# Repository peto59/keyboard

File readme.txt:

to update submodule use:
git submodule update --recursive --remote 

TODO:
Add/Move FN to left
Put key names on silkscreen
Rename win2 to menu key
Fix space between arrows, F keys, printscreen, end/home
Leave space for cable between raspberry pi pico and jack female connector
Add I2C pullup resistors to main board
Make bottom part of case thicker (too much bending currently)
Leave larger toleracnes in all parts
Try to switch to more common screws/bolts/hardware (atleast M3)

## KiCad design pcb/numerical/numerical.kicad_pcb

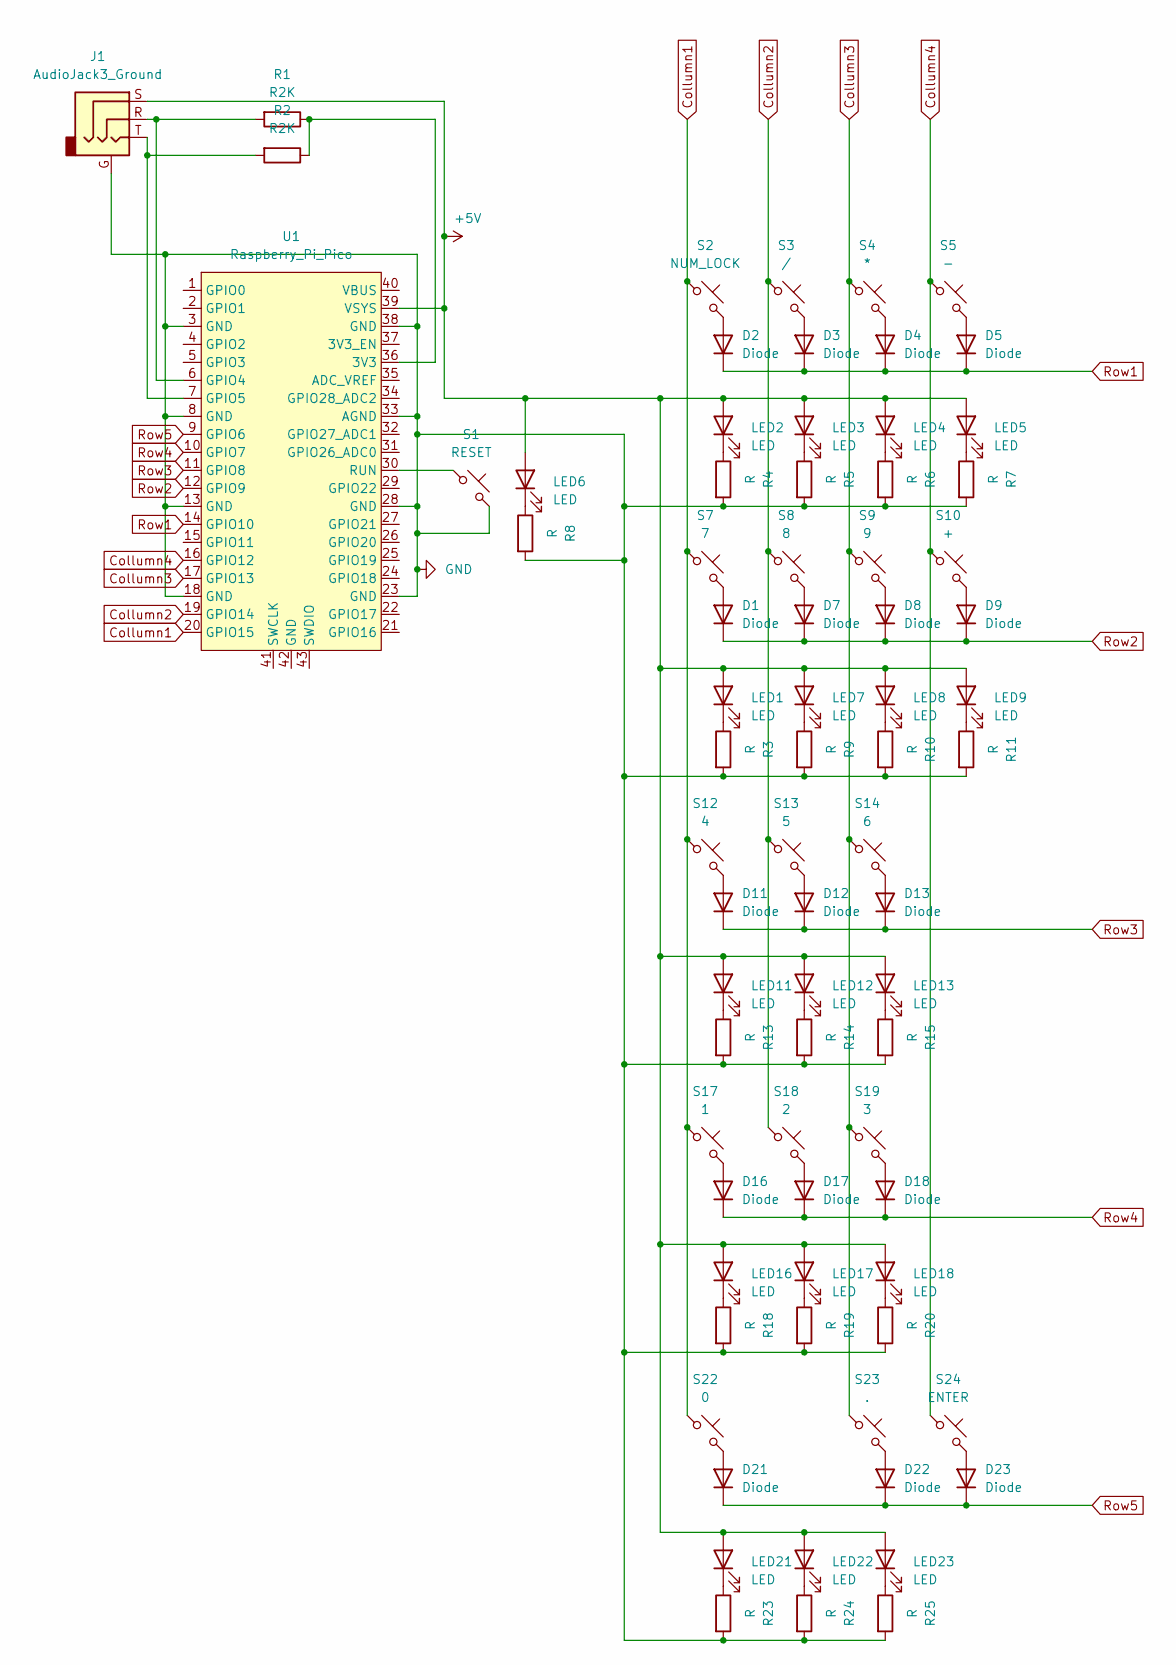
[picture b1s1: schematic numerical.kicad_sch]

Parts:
D1, D2, D3, D4, D5, D7, D8, D9, D11, D12, D13, D16, D17, D18, D21, D22, D23: Diode; Nexperia_CFP3_SOD-123W
J1: AudioJack3_Ground; Jack_3.5mm_KoreanHropartsElec_PJ-320D-4A_Horizontal
LED1, LED2, LED3, LED4, LED5, LED6, LED7, LED8, LED9, LED11, LED12, LED13, LED16, LED17, LED18, LED21, LED22, LED23: LED; MX-LED-PolarityMarked
R1, R2: R2K; R_Axial_DIN0207_L6.3mm_D2.5mm_P10.16mm_Horizontal
R3, R4, R5, R6, R7, R8, R9, R10, R11, R13, R14, R15, R18, R19, R20, R23, R24, R25: R; R_0603_1608Metric_Pad0.98x0.95mm_HandSolder
S1: RESET; MX-Hotswap-1U
S2: NUM_LOCK; MX-Hotswap-1U
S3: /; MX-Hotswap-1U
S4: *; MX-Hotswap-1U
S5: -; MX-Hotswap-1U
S7: 7; MX-Hotswap-1U
S8: 8; MX-Hotswap-1U
S9: 9; MX-Hotswap-1U
S10: +; MX-Hotswap-2U-Vertical
S12: 4; MX-Hotswap-1U
S13: 5; MX-Hotswap-1U
S14: 6; MX-Hotswap-1U
S17: 1; MX-Hotswap-1U
S18: 2; MX-Hotswap-1U
S19: 3; MX-Hotswap-1U
S22: 0; MX-Hotswap-2U
S23: .; MX-Hotswap-1U
S24: ENTER; MX-Hotswap-2U-Vertical
U1: Raspberry_Pi_Pico

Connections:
+5V: J1.S, LED1.2 (A), LED2.2 (A), LED3.2 (A), LED4.2 (A), LED5.2 (A), LED6.2 (A), LED7.2 (A), LED8.2 (A), LED9.2 (A), LED11.2 (A), LED12.2 (A), LED13.2 (A), LED16.2 (A), LED17.2 (A), LED18.2 (A), LED21.2 (A), LED22.2 (A), LED23.2 (A), U1.39 (VSYS)
Collumn1: S2.1, S7.1, S12.1, S17.1, S22.1, U1.20 (GPIO15)
Collumn2: S3.1, S8.1, S13.1, S18.1, U1.19 (GPIO14)
Collumn3: S4.1, S9.1, S14.1, S19.1, S23.1, U1.17 (GPIO13)
Collumn4: S5.1, S10.1, S24.1, U1.16 (GPIO12)
GND: J1.G, R3.2, R4.2, R5.2, R6.2, R7.2, R8.2, R9.2, R10.2, R11.2, R13.2, R14.2, R15.2, R18.2, R19.2, R20.2, R23.2, R24.2, R25.2, S1.2, U1.3 (GND), U1.8 (GND), U1.13 (GND), U1.18 (GND), U1.23 (GND), U1.28 (GND), U1.33 (AGND), U1.38 (GND)
unnamed: D1.2 (A), S7.2
unnamed: D2.2 (A), S2.2
unnamed: D3.2 (A), S3.2
unnamed: D4.2 (A), S4.2
unnamed: D5.2 (A), S5.2
unnamed: D7.2 (A), S8.2
unnamed: D8.2 (A), S9.2
unnamed: D9.2 (A), S10.2
unnamed: D11.2 (A), S12.2
unnamed: D12.2 (A), S13.2
unnamed: D13.2 (A), S14.2
unnamed: D16.2 (A), S17.2
unnamed: D17.2 (A), S18.2
unnamed: D18.2 (A), S19.2
unnamed: D21.2 (A), S22.2
unnamed: D22.2 (A), S23.2
unnamed: D23.2 (A), S24.2
unnamed: LED1.1 (K), R3.1
unnamed: LED2.1 (K), R4.1
unnamed: LED3.1 (K), R5.1
unnamed: LED4.1 (K), R6.1
unnamed: LED5.1 (K), R7.1
unnamed: LED6.1 (K), R8.1
unnamed: LED7.1 (K), R9.1
unnamed: LED8.1 (K), R10.1
unnamed: LED9.1 (K), R11.1
unnamed: LED11.1 (K), R13.1
unnamed: LED12.1 (K), R14.1
unnamed: LED13.1 (K), R15.1
unnamed: LED16.1 (K), R18.1
unnamed: LED17.1 (K), R19.1
unnamed: LED18.1 (K), R20.1
unnamed: LED21.1 (K), R23.1
unnamed: LED22.1 (K), R24.1
unnamed: LED23.1 (K), R25.1
unnamed: R1.1, R2.1, U1.36 (3V3)
unnamed: J1.R, R1.2, U1.6 (GPIO4)
unnamed: J1.T, R2.2, U1.7 (GPIO5)
unnamed: S1.1, U1.30 (RUN)
Row1: D2.1 (K), D3.1 (K), D4.1 (K), D5.1 (K), U1.14 (GPIO10)
Row2: D1.1 (K), D7.1 (K), D8.1 (K), D9.1 (K), U1.12 (GPIO9)
Row3: D11.1 (K), D12.1 (K), D13.1 (K), U1.11 (GPIO8)
Row4: D16.1 (K), D17.1 (K), D18.1 (K), U1.10 (GPIO7)
Row5: D21.1 (K), D22.1 (K), D23.1 (K), U1.9 (GPIO6)

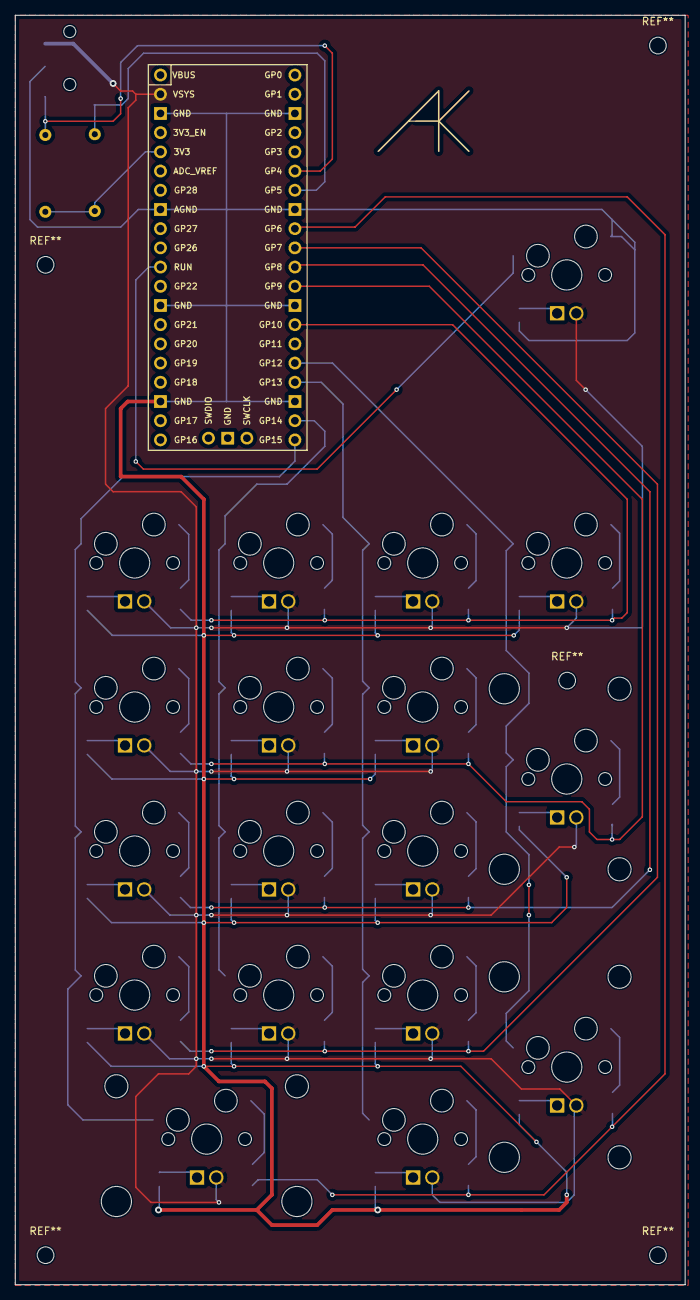
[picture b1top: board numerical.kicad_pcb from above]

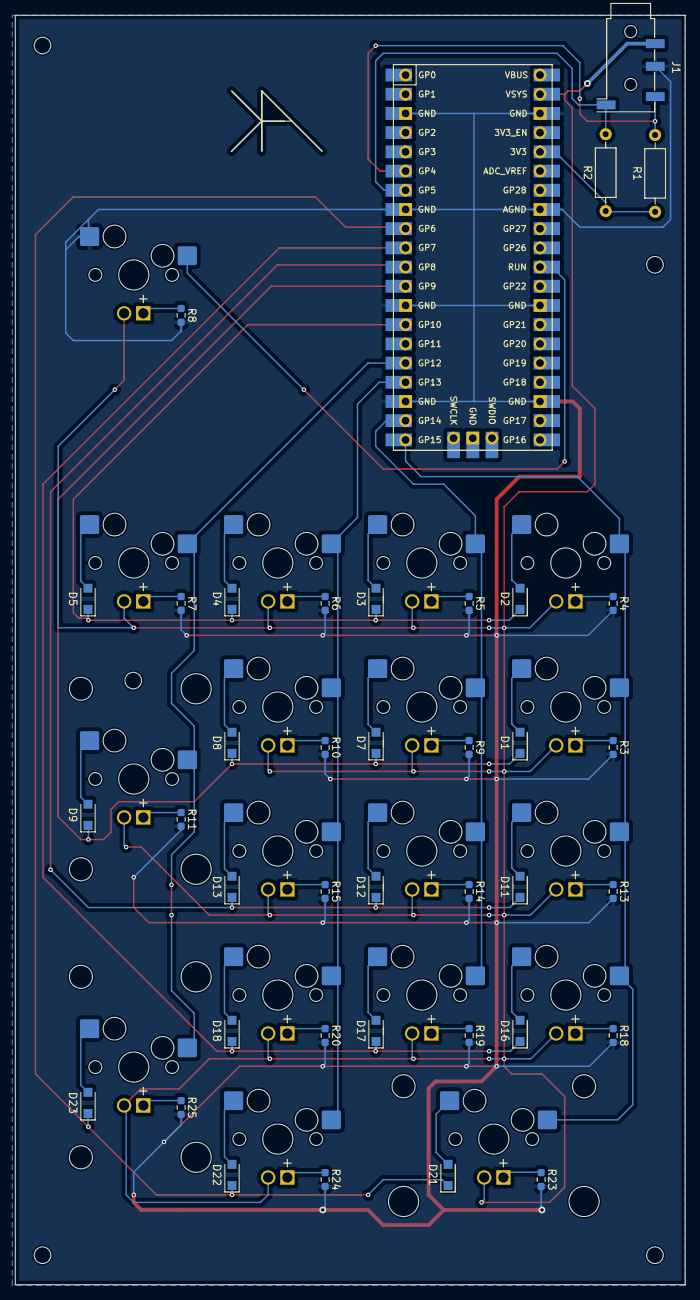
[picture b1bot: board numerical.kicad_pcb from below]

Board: 2 copper layers, 88.6 x 167.9 mm, 75 parts (39 on the bottom side), 50 nets.

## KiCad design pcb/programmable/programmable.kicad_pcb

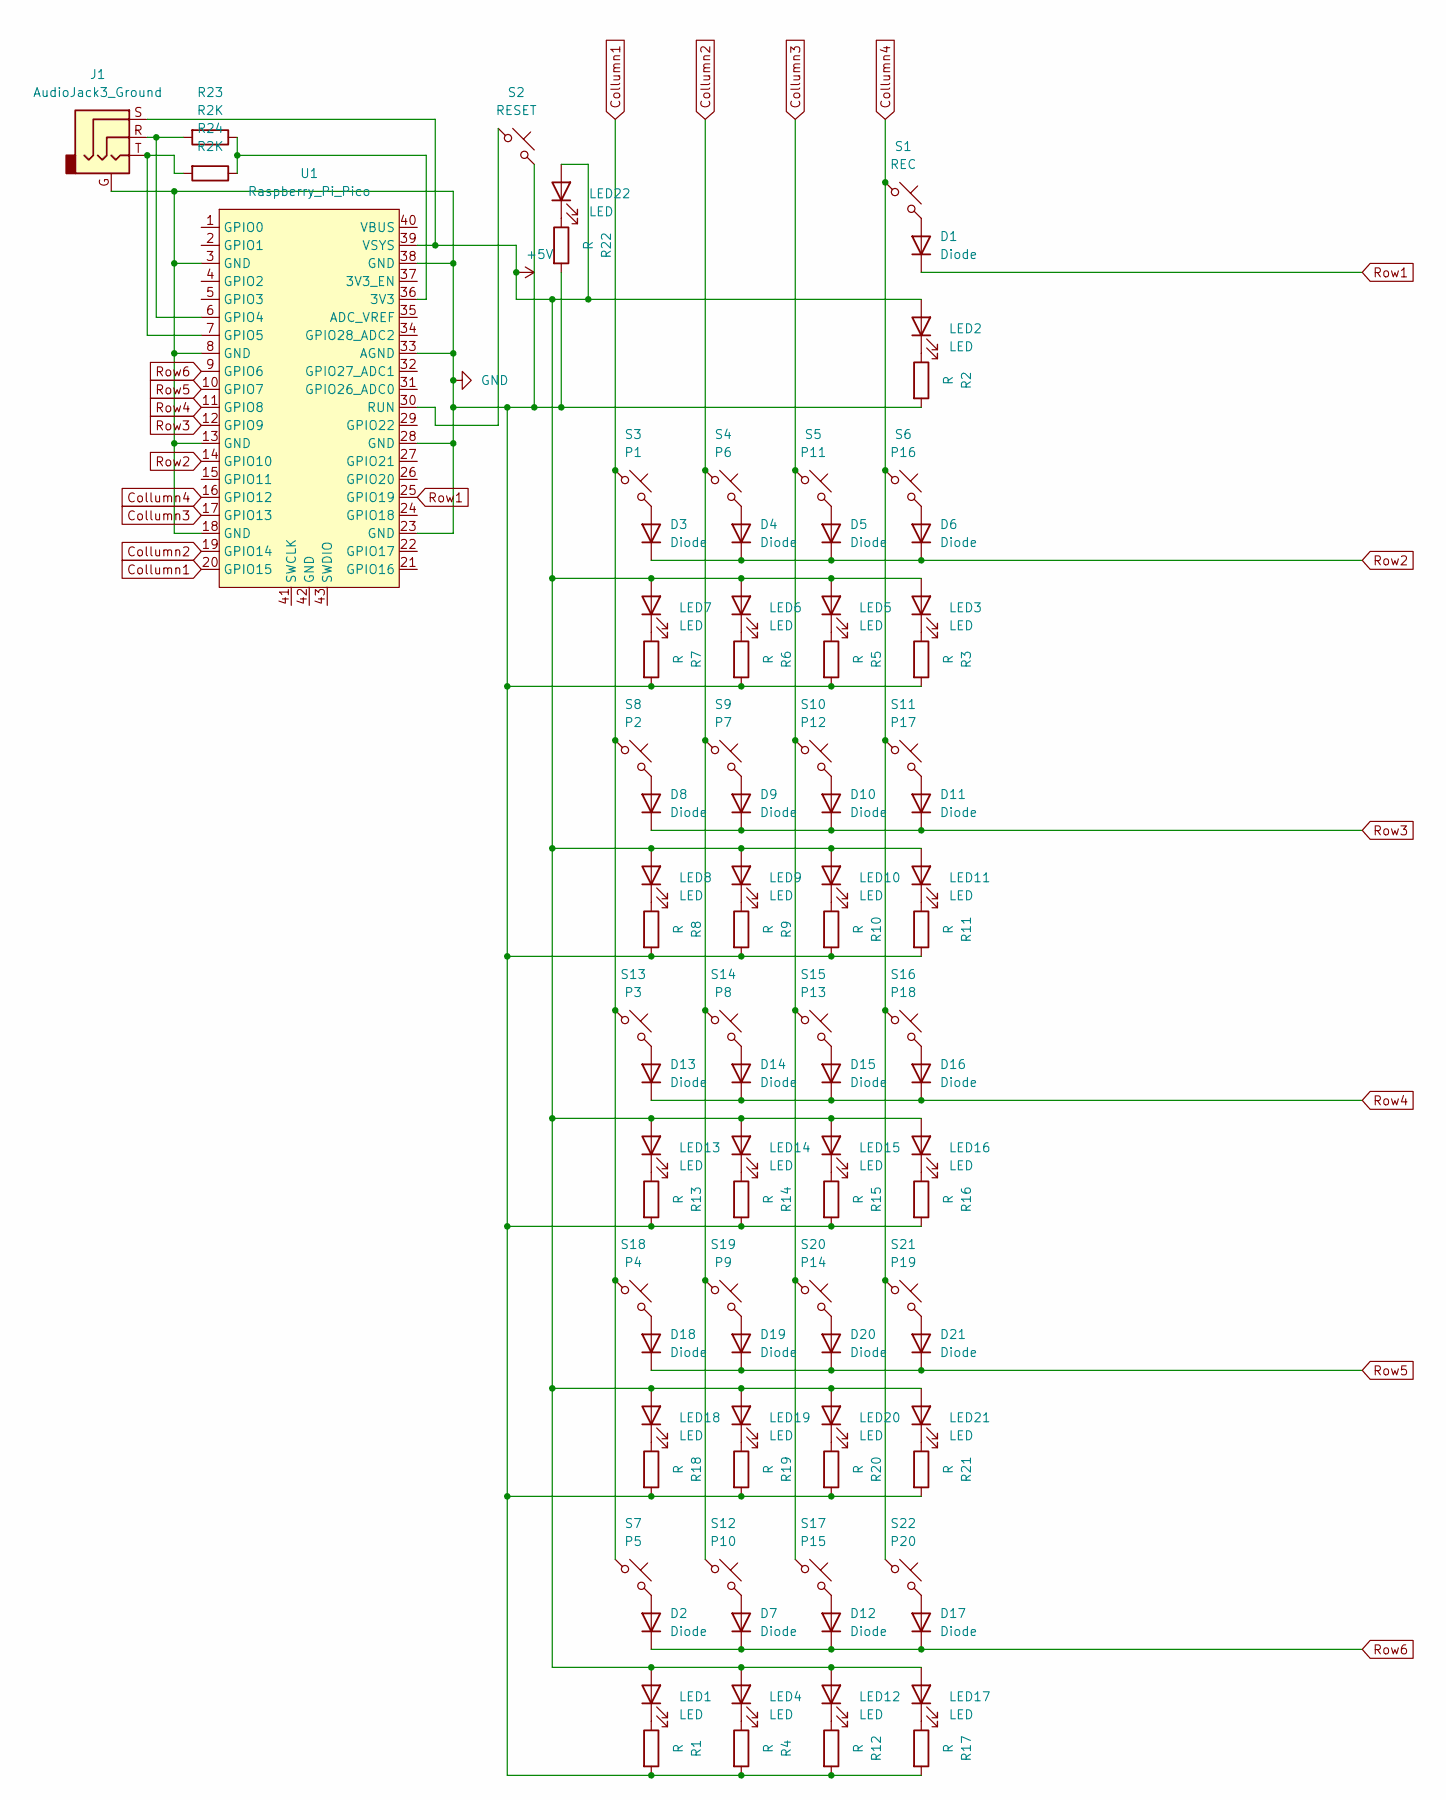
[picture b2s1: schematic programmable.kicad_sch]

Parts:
D1, D2, D3, D4, D5, D6, D7, D8, D9, D10, D11, D12, D13, D14, D15, D16, D17, D18, D19, D20, D21: Diode; Nexperia_CFP3_SOD-123W
J1: AudioJack3_Ground; Jack_3.5mm_KoreanHropartsElec_PJ-320D-4A_Horizontal
LED1, LED2, LED3, LED4, LED5, LED6, LED7, LED8, LED9, LED10, LED11, LED12, LED13, LED14, LED15, LED16, LED17, LED18, LED19, LED20, LED21, LED22: LED; MX-LED-PolarityMarked
R1, R2, R3, R4, R5, R6, R7, R8, R9, R10, R11, R12, R13, R14, R15, R16, R17, R18, R19, R20, R21, R22: R; R_0603_1608Metric_Pad0.98x0.95mm_HandSolder
R23, R24: R2K; R_Axial_DIN0207_L6.3mm_D2.5mm_P10.16mm_Horizontal
S1: REC; MX-Hotswap-1U
S2: RESET; MX-Hotswap-1U
S3: P1; MX-Hotswap-1U
S4: P6; MX-Hotswap-1U
S5: P11; MX-Hotswap-1U
S6: P16; MX-Hotswap-1U
S7: P5; MX-Hotswap-1U
S8: P2; MX-Hotswap-1U
S9: P7; MX-Hotswap-1U
S10: P12; MX-Hotswap-1U
S11: P17; MX-Hotswap-1U
S12: P10; MX-Hotswap-1U
S13: P3; MX-Hotswap-1U
S14: P8; MX-Hotswap-1U
S15: P13; MX-Hotswap-1U
S16: P18; MX-Hotswap-1U
S17: P15; MX-Hotswap-1U
S18: P4; MX-Hotswap-1U
S19: P9; MX-Hotswap-1U
S20: P14; MX-Hotswap-1U
S21: P19; MX-Hotswap-1U
S22: P20; MX-Hotswap-1U
U1: Raspberry_Pi_Pico

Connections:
+5V: J1.S, LED1.2 (A), LED2.2 (A), LED3.2 (A), LED4.2 (A), LED5.2 (A), LED6.2 (A), LED7.2 (A), LED8.2 (A), LED9.2 (A), LED10.2 (A), LED11.2 (A), LED12.2 (A), LED13.2 (A), LED14.2 (A), LED15.2 (A), LED16.2 (A), LED17.2 (A), LED18.2 (A), LED19.2 (A), LED20.2 (A), LED21.2 (A), LED22.2 (A), U1.39 (VSYS)
Collumn1: S3.1, S7.1, S8.1, S13.1, S18.1, U1.20 (GPIO15)
Collumn2: S4.1, S9.1, S12.1, S14.1, S19.1, U1.19 (GPIO14)
Collumn3: S5.1, S10.1, S15.1, S17.1, S20.1, U1.17 (GPIO13)
Collumn4: S1.1, S6.1, S11.1, S16.1, S21.1, S22.1, U1.16 (GPIO12)
GND: J1.G, R1.2, R2.2, R3.2, R4.2, R5.2, R6.2, R7.2, R8.2, R9.2, R10.2, R11.2, R12.2, R13.2, R14.2, R15.2, R16.2, R17.2, R18.2, R19.2, R20.2, R21.2, R22.2, S2.2, U1.3 (GND), U1.8 (GND), U1.13 (GND), U1.18 (GND), U1.23 (GND), U1.28 (GND), U1.33 (AGND), U1.38 (GND)
unnamed: D1.2 (A), S1.2
unnamed: D2.2 (A), S7.2
unnamed: D3.2 (A), S3.2
unnamed: D4.2 (A), S4.2
unnamed: D5.2 (A), S5.2
unnamed: D6.2 (A), S6.2
unnamed: D7.2 (A), S12.2
unnamed: D8.2 (A), S8.2
unnamed: D9.2 (A), S9.2
unnamed: D10.2 (A), S10.2
unnamed: D11.2 (A), S11.2
unnamed: D12.2 (A), S17.2
unnamed: D13.2 (A), S13.2
unnamed: D14.2 (A), S14.2
unnamed: D15.2 (A), S15.2
unnamed: D16.2 (A), S16.2
unnamed: D17.2 (A), S22.2
unnamed: D18.2 (A), S18.2
unnamed: D19.2 (A), S19.2
unnamed: D20.2 (A), S20.2
unnamed: D21.2 (A), S21.2
unnamed: LED1.1 (K), R1.1
unnamed: LED2.1 (K), R2.1
unnamed: LED3.1 (K), R3.1
unnamed: LED4.1 (K), R4.1
unnamed: LED5.1 (K), R5.1
unnamed: LED6.1 (K), R6.1
unnamed: LED7.1 (K), R7.1
unnamed: LED8.1 (K), R8.1
unnamed: LED9.1 (K), R9.1
unnamed: LED10.1 (K), R10.1
unnamed: LED11.1 (K), R11.1
unnamed: LED12.1 (K), R12.1
unnamed: LED13.1 (K), R13.1
unnamed: LED14.1 (K), R14.1
unnamed: LED15.1 (K), R15.1
unnamed: LED16.1 (K), R16.1
unnamed: LED17.1 (K), R17.1
unnamed: LED18.1 (K), R18.1
unnamed: LED19.1 (K), R19.1
unnamed: LED20.1 (K), R20.1
unnamed: LED21.1 (K), R21.1
unnamed: LED22.1 (K), R22.1
unnamed: R23.1, R24.1, U1.36 (3V3)
unnamed: J1.R, R23.2, U1.6 (GPIO4)
unnamed: J1.T, R24.2, U1.7 (GPIO5)
unnamed: S2.1, U1.30 (RUN)
Row1: D1.1 (K), U1.25 (GPIO19)
Row2: D3.1 (K), D4.1 (K), D5.1 (K), D6.1 (K), U1.14 (GPIO10)
Row3: D8.1 (K), D9.1 (K), D10.1 (K), D11.1 (K), U1.12 (GPIO9)
Row4: D13.1 (K), D14.1 (K), D15.1 (K), D16.1 (K), U1.11 (GPIO8)
Row5: D18.1 (K), D19.1 (K), D20.1 (K), D21.1 (K), U1.10 (GPIO7)
Row6: D2.1 (K), D7.1 (K), D12.1 (K), D17.1 (K), U1.9 (GPIO6)

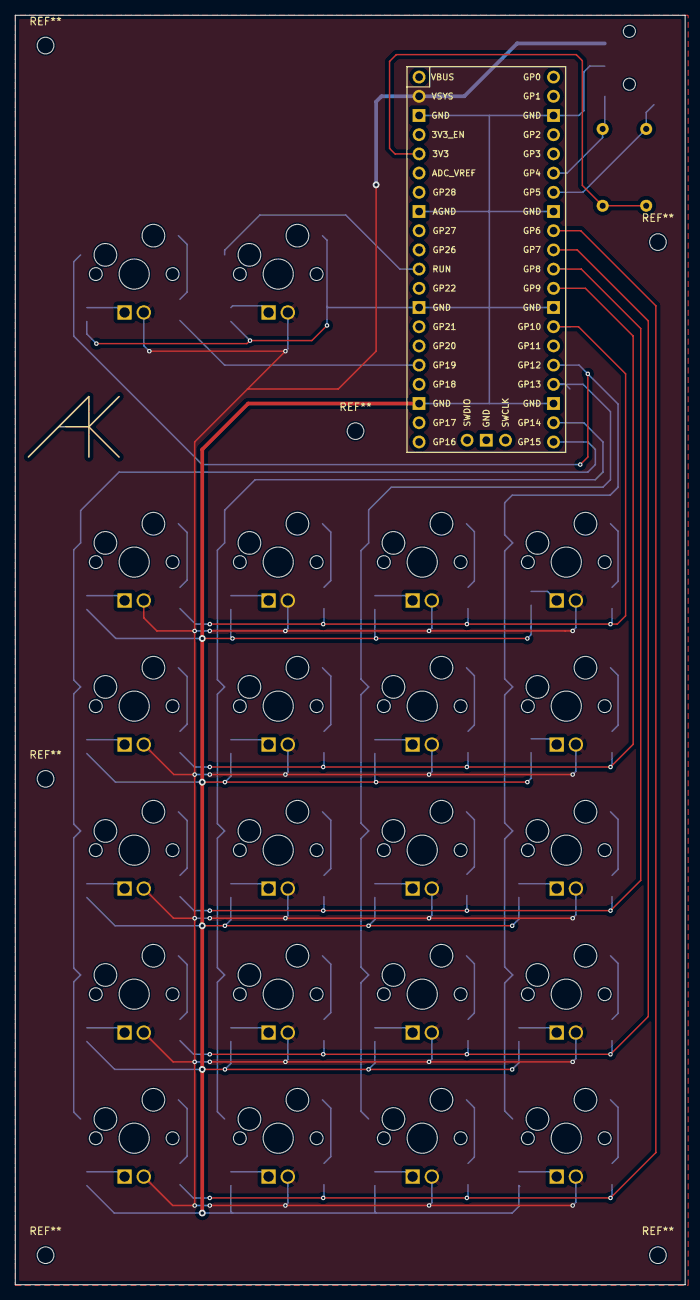
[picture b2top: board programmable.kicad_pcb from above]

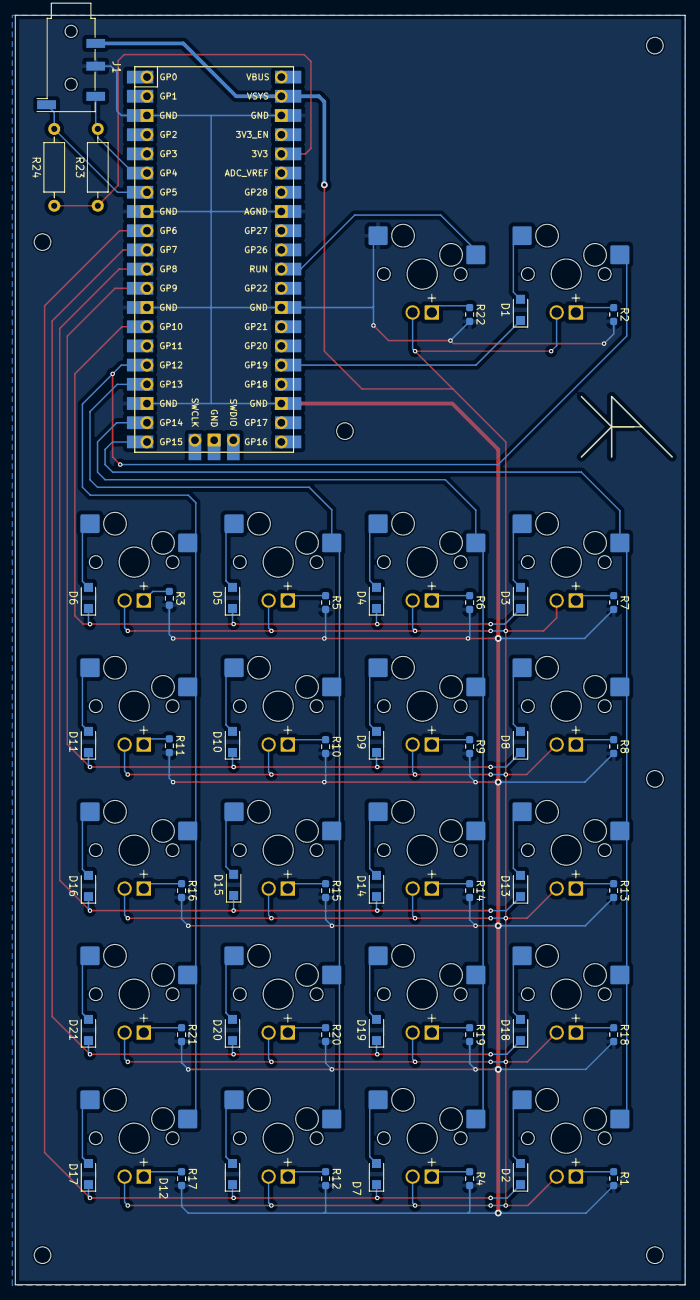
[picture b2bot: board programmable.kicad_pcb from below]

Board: 2 copper layers, 88.6 x 167.9 mm, 91 parts (47 on the bottom side), 59 nets.

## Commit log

2024-07-23 programmable PCB done
2024-07-23 numerical done
2024-07-23 added copper zone fills
2024-07-23 small layout edits for stl generation
2024-07-23 added stl generator submodule
2024-07-24 gerber files
2024-07-27 submodules added
2024-07-27 Update slave_firmware
2024-07-27 rename submodules
2024-07-27 remade submodules
2024-07-27 reorganization
2024-07-27 tips
2024-09-08 nummerical plate + case
2025-01-25 move layout to start at y offset 0
